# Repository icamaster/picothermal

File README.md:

# Introduction

Picothermal is a WebUSB thermal camera based on a Flir Lepton 3.5 sensor that uses a RP2040 and connects to your PC or phone via USB-C. 

It doesn't need any app as it uses WebUSB (which also means it doesn't support Firefox, unfortunately). 

*Top assembly*

[*WebUSB app*](#firmware)

# Hardware

The hardware and software is open-source, see the [picothermal-hardware](picothermal-hardware) folder for the Kicad project, manufacturing files and a PDF schematic. 

There are also STLs available for an enclosure in [enclosure](enclosure). There are two variants for the bottom piece depending on the PCB thickness (0.8mm or 1.6mm).

# Firmware

For firmware, please see [picothermal-fw](https://github.com/icamaster/picothermal-fw).

Initially I wanted to write the software in C, using TinyUSB for the USB protocol. Unfortunately, due to lack of free time, I decided to rewrite this using agents in Rust, using embassy. The end result works quite good, although I expect the code to be pretty unmaintanable since it is mostly agent written.

# License

MIT

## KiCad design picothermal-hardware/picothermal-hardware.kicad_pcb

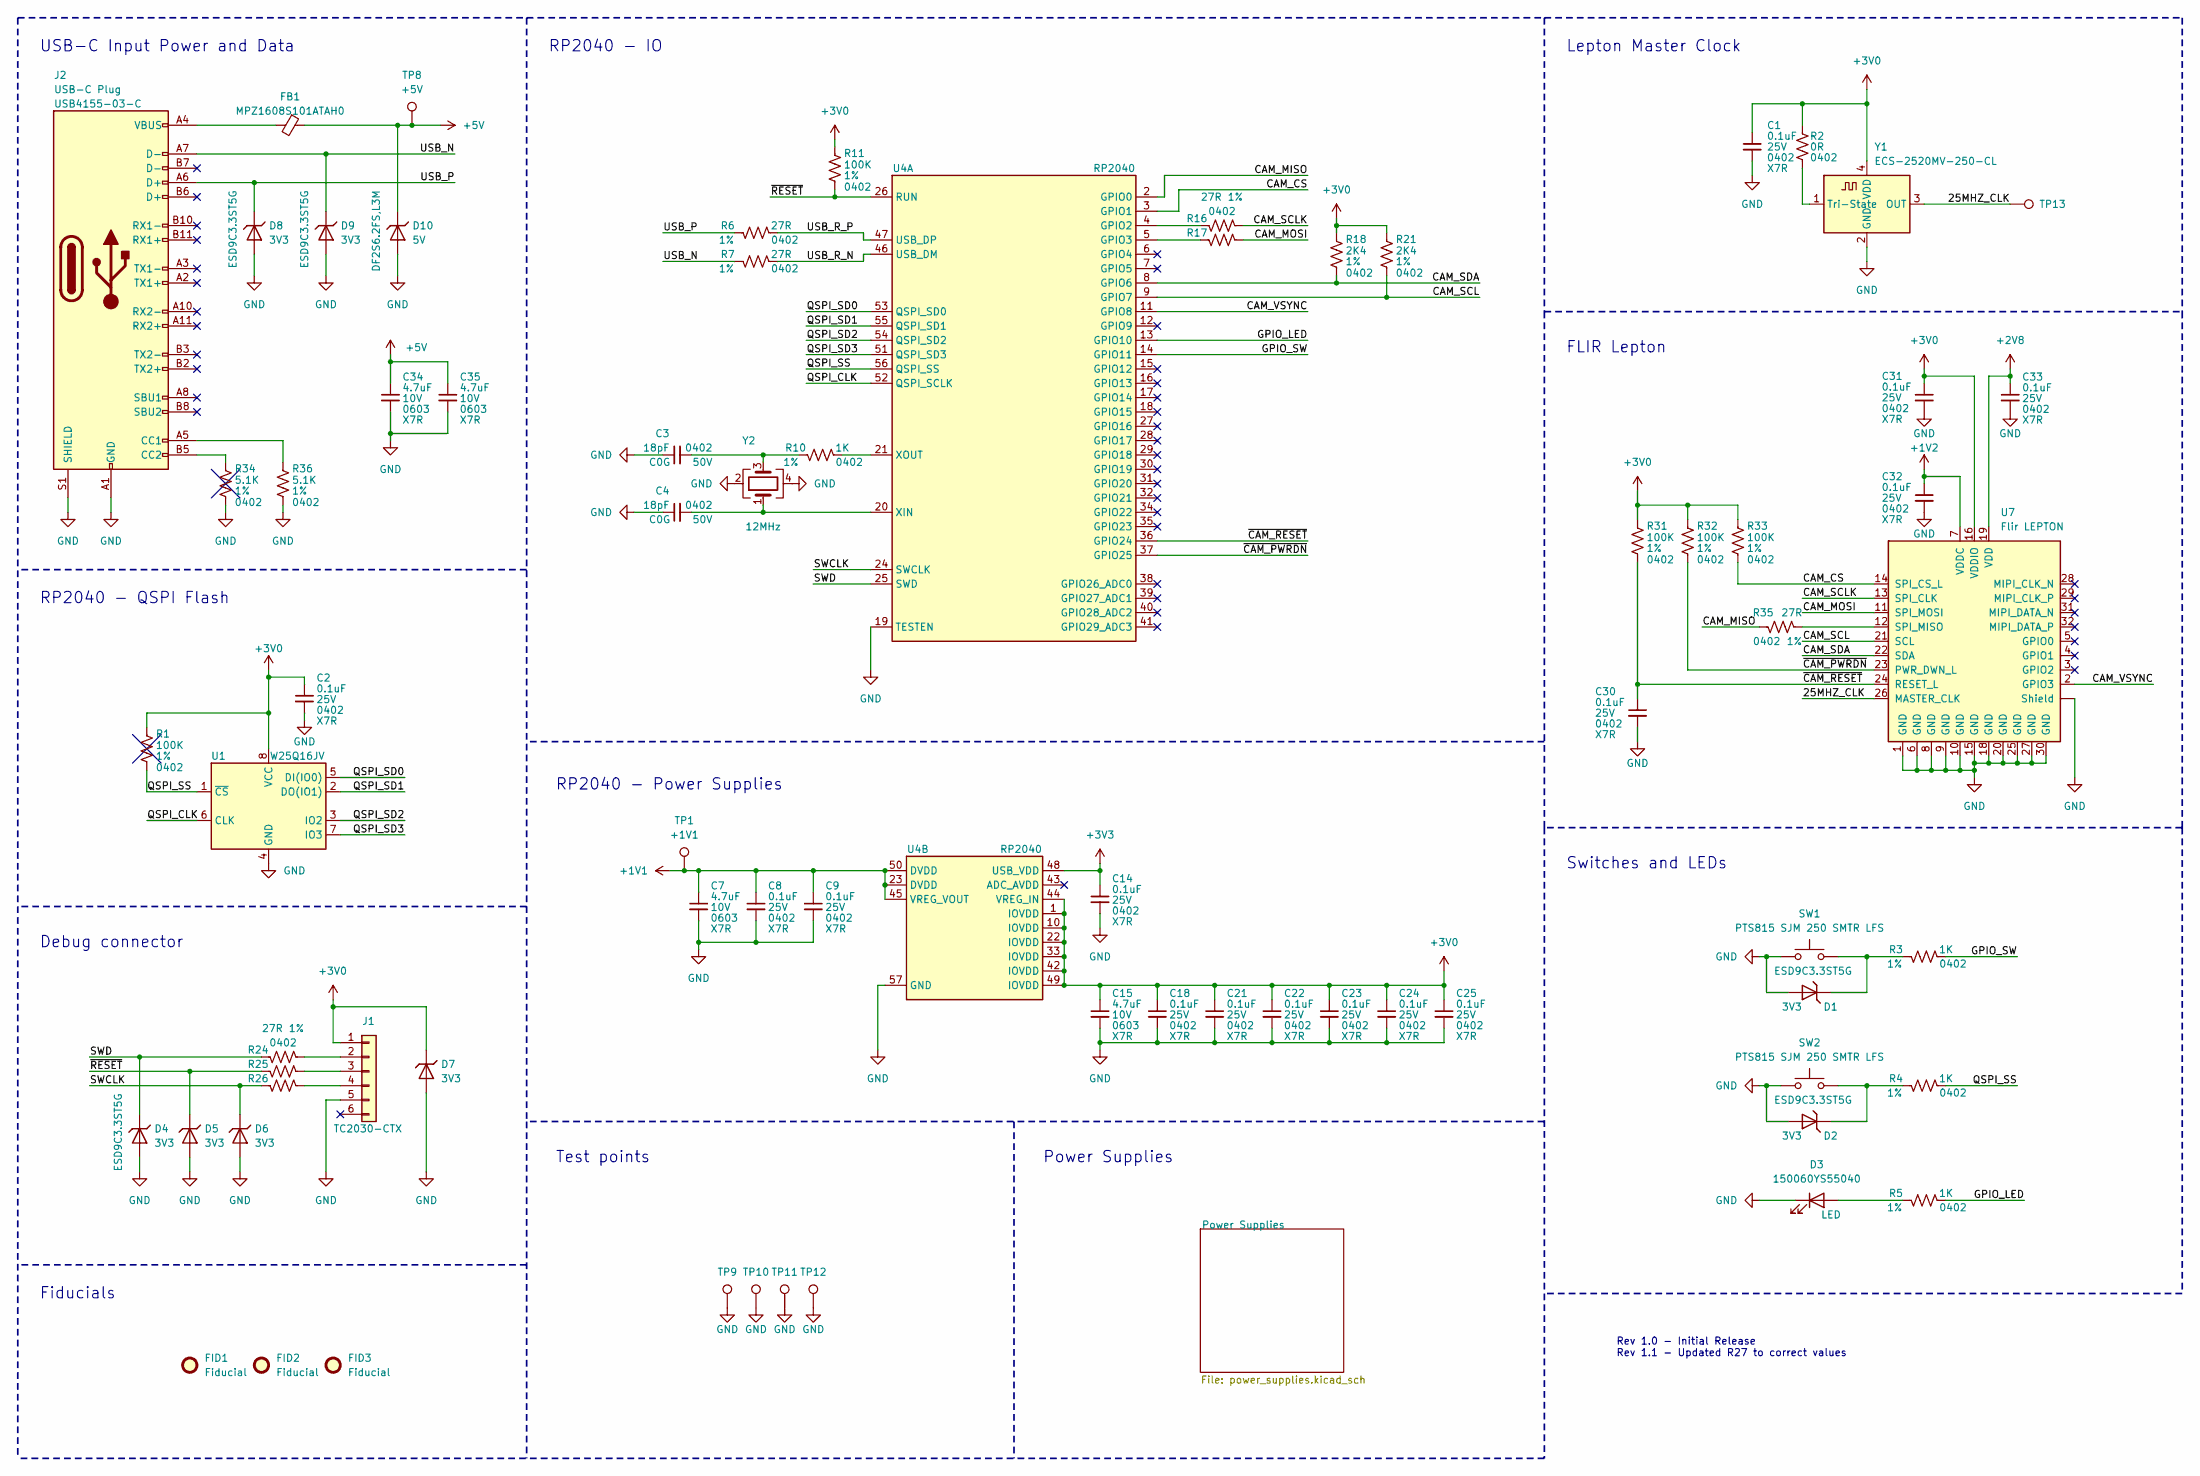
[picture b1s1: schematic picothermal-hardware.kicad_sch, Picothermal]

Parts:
C1, C2, C8, C9, C14, C18, C21, C22, C23, C24, C25, C30, C31, C32, C33: 0.1uF; C_0402_1005Metric; Voltage Rating 25V
C3, C4: 18pF; C_0402_1005Metric; Voltage Rating 50V
C7, C15, C34, C35: 4.7uF; C_0603_1608Metric; Voltage Rating 10V
D1, D2, D4, D5, D6, D7, D8, D9: ESD9C3.3ST5G; D_SOD-923; Part Number ESD9C3.3ST5G
D3: LED; LED_0603_1608Metric; Part Number 150060YS55040
D10: DF2S6.2FS,L3M; D_SOD-923; Part Number DF2S6.2FS,L3M
FB1: MPZ1608S101ATAH0; L_0603_1608Metric; Part Number MPZ1608S101ATAH0
FID1, FID2, FID3: Fiducial; Fiducial_1mm_Mask2mm
J1: TC2030-CTX; Tag-Connect_TC2030-IDC-NL_2x03_P1.27mm_Vertical
J2: USB-C Plug; USB_C_Plug_GCT_USB4155; Part Number USB4155-03-C
R1, R11, R31, R32, R33: 100K; R_0402_1005Metric; Tolerance 1%
R2: 0R; R_0402_1005Metric; Tolerance 1%
R3, R4, R5, R10: 1K; R_0402_1005Metric; Tolerance 1%
R6, R7, R16, R17, R24, R25, R26, R35: 27R; R_0402_1005Metric; Tolerance 1%
R18, R21: 2K4; R_0402_1005Metric; Tolerance 1%
R34, R36: 5.1K; R_0402_1005Metric; Tolerance 1%
SW1, SW2: SW_Push; SW_SPST_PTS815; Part Number PTS815 SJM 250 SMTR LFS
TP1: +1V1; TestPoint_Pad_D1.0mm
TP8: +5V; TestPoint_Pad_D1.0mm
TP9, TP10, TP12: GND; TestPoint_Pad_D1.0mm
TP11: GND; TestPoint_Plated_Slot_5.0x2.5
TP13: 25MHz; TestPoint_Pad_D1.0mm
U1: W25Q16JV; USON-8_2x3mm; Part Number W25Q16JVUXIQ
U4: RP2040; QFN-56-1EP_7x7mm_P0.4mm_EP3.2x3.2mm; Part Number RP2040
U7: Flir LEPTON; MOLEX_105028-1001; Part Number 105028-1001
Y1: ECS-2520MV-250-CL; Oscillator_SMD_ECS_2520MV-xxx-xx-4Pin_2.5x2.0mm
Y2: 12MHz; Crystal_SMD_2520-4Pin_2.5x2.0mm; Part Number ECS-120-12-36-AGN-TR3

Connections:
+1V1: C7.1, C8.1, C9.1, TP1.1, U4.23 (DVDD), U4.45 (VREG_VOUT), U4.50 (DVDD)
+1V2: C32.1, U7.7 (VDDC); also elsewhere on the board
+2V8: C33.1, U7.19 (VDD); also elsewhere on the board
+3V0: C1.1, C2.1, C15.1, C18.1, C21.1, C22.1, C23.1, C24.1, C25.1, C31.1, D7.1 (K), J1.1, R1.1, R2.1, R11.1, R18.1, R21.1, R31.1, R32.1, R33.1, U1.8 (VCC), U4.1 (IOVDD), U4.10 (IOVDD), U4.22 (IOVDD), U4.33 (IOVDD), U4.42 (IOVDD), U4.44 (VREG_IN), U4.49 (IOVDD), U7.16 (VDDIO), Y1.4 (VDD); also elsewhere on the board
+3V3: C14.1, U4.48 (USB_VDD); also elsewhere on the board
+5V: C34.1, C35.1, D10.1 (K), FB1.1, TP8.1; also elsewhere on the board
/25MHZ_CLK: TP13.1, U7.26 (MASTER_CLK), Y1.3 (OUT)
/CAM_CS: R33.2, U4.3 (GPIO1), U7.14 (SPI_CS_L)
/CAM_MISO: R35.2, U4.2 (GPIO0)
/CAM_MOSI: R17.1, U7.11 (SPI_MOSI)
/CAM_SCL: R21.2, U4.9 (GPIO7), U7.21 (SCL)
/CAM_SCLK: R16.1, U7.13 (SPI_CLK)
/CAM_SDA: R18.2, U4.8 (GPIO6), U7.22 (SDA)
/CAM_VSYNC: U4.11 (GPIO8), U7.2 (GPIO3)
/GPIO_LED: R5.1, U4.13 (GPIO10)
/GPIO_SW: R3.1, U4.14 (GPIO11)
/QSPI_CLK: U1.6 (CLK), U4.52 (QSPI_SCLK)
/QSPI_SD0: U1.5 (DI(IO0)), U4.53 (QSPI_SD0)
/QSPI_SD1: U1.2 (DO(IO1)), U4.55 (QSPI_SD1)
/QSPI_SD2: U1.3 (IO2), U4.54 (QSPI_SD2)
/QSPI_SD3: U1.7 (IO3), U4.51 (QSPI_SD3)
/QSPI_SS: R1.2, R4.1, U1.1 (~CS), U4.56 (QSPI_SS)
/SWCLK: D6.1 (K), R26.2, U4.24 (SWCLK)
/SWD: D4.1 (K), R24.2, U4.25 (SWD)
/USB_N: D9.1 (K), J2.A7 (D-), R7.2
/USB_P: D8.1 (K), J2.A6 (D+), R6.2
/USB_R_N: R7.1, U4.46 (USB_DM)
/USB_R_P: R6.1, U4.47 (USB_DP)
/~CAM_PWRDN: R32.2, U4.37 (GPIO25), U7.23 (PWR_DWN_L)
/~CAM_RESET: C30.1, R31.2, U4.36 (GPIO24), U7.24 (RESET_L)
/~RESET: D5.1 (K), R11.2, R25.2, U4.26 (RUN)
GND: C1.2, C2.2, C3.1, C4.1, C7.2, C8.2, C9.2, C14.2, C15.2, C18.2, C21.2, C22.2, C23.2, C24.2, C25.2, C30.2, C31.2, C32.2, C33.2, C34.2, C35.2, D1.2 (A), D2.2 (A), D3.1 (K), D4.2 (A), D5.2 (A), D6.2 (A), D7.2 (A), D8.2 (A), D9.2 (A), D10.2 (A), J1.5, J2.A1 (GND), J2.A12 (GND), J2.B1 (GND), J2.B12 (GND), J2.S1 (SHIELD), R34.2, R36.2, SW1.1, SW2.1, TP9.1, TP10.1, TP11.1, TP12.1, U1.4 (GND), U4.19 (TESTEN), U4.57 (GND), U7.1 (GND), U7.6 (GND), U7.8 (GND), U7.9 (GND), U7.10 (GND), U7.15 (GND), U7.17 (NC), U7.18 (GND), U7.20 (GND), U7.25 (GND), U7.27 (GND), U7.30 (GND), U7.Shield, Y1.2 (GND), Y2.2, Y2.4; also elsewhere on the board
unnamed: C3.2, R10.2, Y2.3
unnamed: D1.1 (K), R3.2, SW1.2
unnamed: D2.1 (K), R4.2, SW2.2
unnamed: D3.2 (A), R5.2
unnamed: FB1.2, J2.A4 (VBUS), J2.A9 (VBUS), J2.B4 (VBUS), J2.B9 (VBUS)
unnamed: J1.2, R24.1
unnamed: J1.3, R25.1
unnamed: J1.4, R26.1
unnamed: J2.A5 (CC1), R36.1
unnamed: J2.B5 (CC2), R34.1
unnamed: R16.2, U4.4 (GPIO2)
unnamed: R17.2, U4.5 (GPIO3)
unnamed: C4.2, U4.20 (XIN), Y2.1
unnamed: R10.1, U4.21 (XOUT)
unnamed: R35.1, U7.12 (SPI_MISO)
unnamed: R2.2, Y1.1 (Tri-State)

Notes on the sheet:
Rev 1.0 - Initial Release Rev 1.1 - Updated R27 to correct values
FLIR Lepton
RP2040 - QSPI Flash
Test points
USB-C Input Power and Data
Fiducials
RP2040 - Power Supplies
Debug connector
Lepton Master Clock
RP2040 - IO
Switches and LEDs
Power Supplies

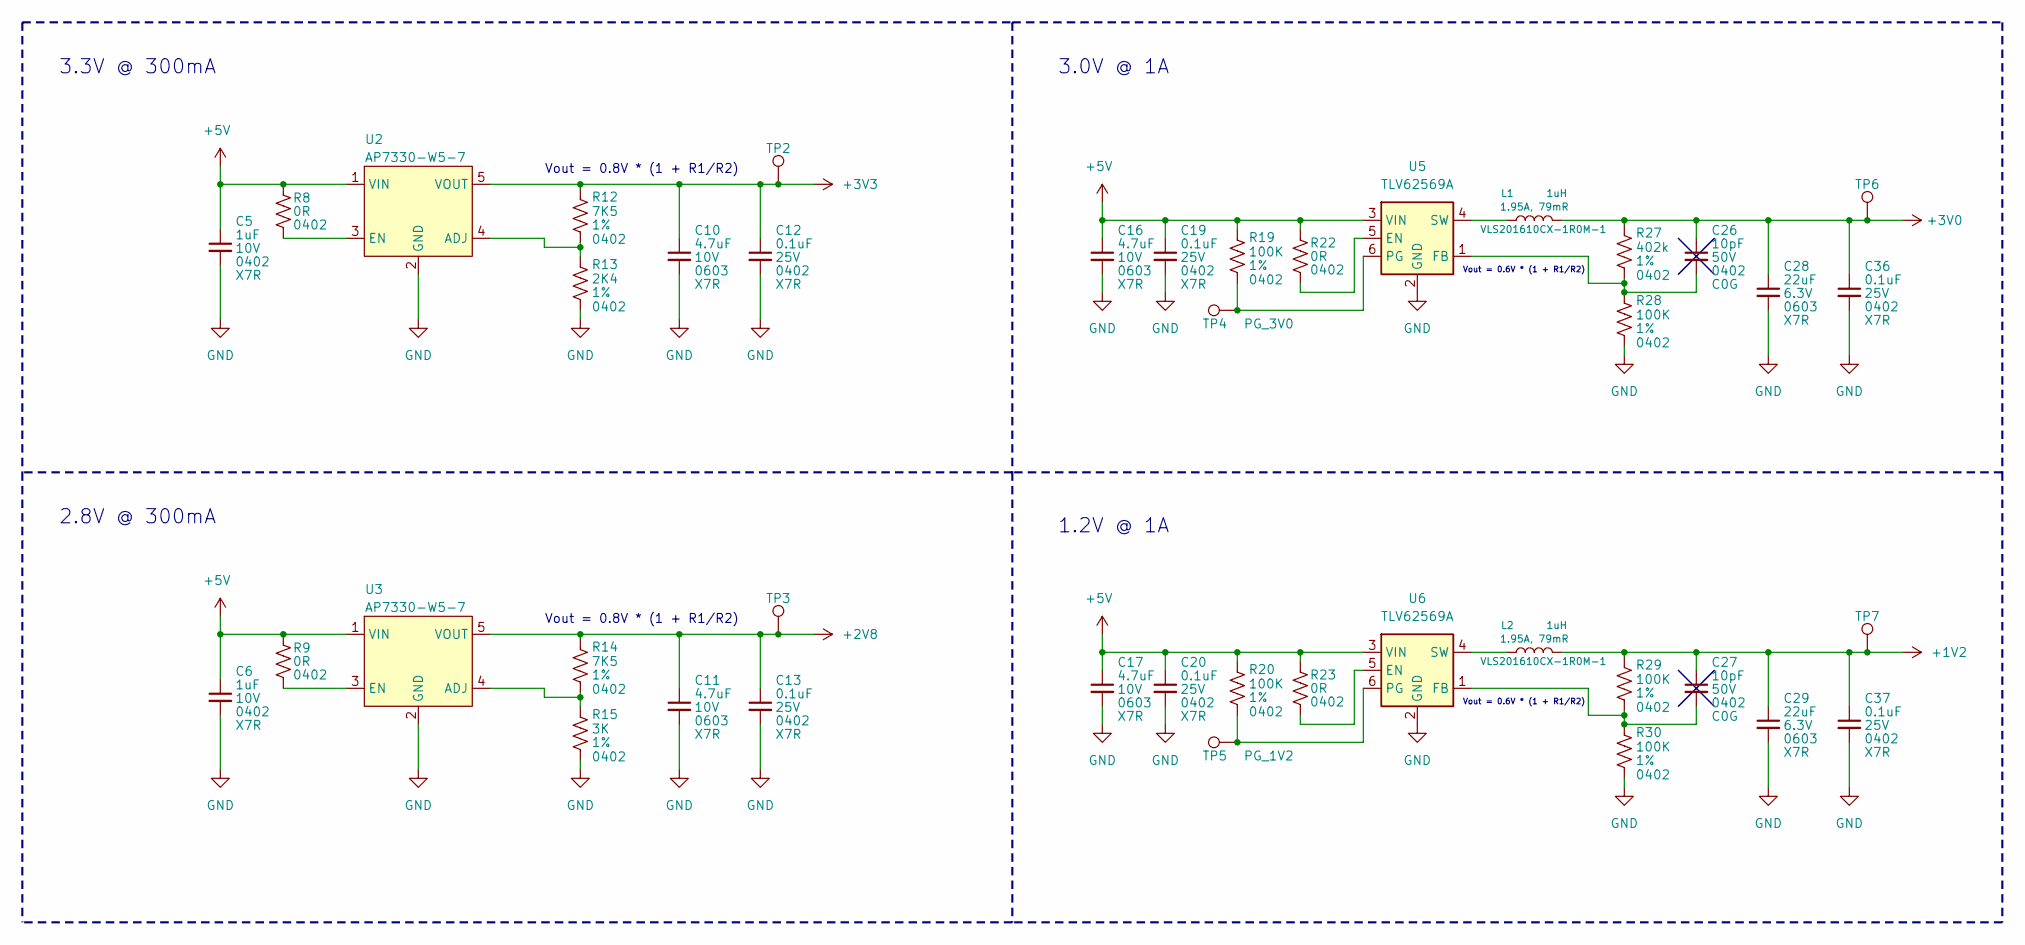
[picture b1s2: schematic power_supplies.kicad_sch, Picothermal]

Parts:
C5, C6: 1uF; C_0402_1005Metric; Voltage Rating 10V
C10, C11, C16, C17: 4.7uF; C_0603_1608Metric; Voltage Rating 10V
C12, C13, C19, C20, C36, C37: 0.1uF; C_0402_1005Metric; Voltage Rating 25V
C26, C27: 10pF; C_0402_1005Metric; Voltage Rating 50V
C28, C29: 22uF; C_0603_1608Metric; Voltage Rating 6.3V
L1, L2: 1uH; L_TDK_VLS201610CX-1; Part Number VLS201610CX-1R0M-1
R8, R9, R22, R23: 0R; R_0402_1005Metric; Tolerance 1%
R12, R14: 7K5; R_0402_1005Metric; Tolerance 1%
R13: 2K4; R_0402_1005Metric; Tolerance 1%
R15: 3K; R_0402_1005Metric; Tolerance 1%
R19, R20, R28, R29, R30: 100K; R_0402_1005Metric; Tolerance 1%
R27: 402k; R_0402_1005Metric; Tolerance 1%
TP2: 3V3; TestPoint_Pad_D1.0mm
TP3: 2V8; TestPoint_Pad_D1.0mm
TP4: PG_3V0; TestPoint_Pad_D1.0mm
TP5: PG_1V2; TestPoint_Pad_D1.0mm
TP6: 3V0; TestPoint_Pad_D1.0mm
TP7: 1V2; TestPoint_Pad_D1.0mm
U2, U3: AP7330-W5-7; SOT-25-5; Part Number AP7330-W5-7
U5, U6: TLV62569A; SOT-563; Part Number TLV62569APDRLR

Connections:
+1V2: C27.1, C29.1, C37.1, L2.2, R29.1, TP7.1; also elsewhere on the board
+2V8: C11.1, C13.1, R14.1, TP3.1, U3.5 (VOUT); also elsewhere on the board
+3V0: C26.1, C28.1, C36.1, L1.2, R27.1, TP6.1; also elsewhere on the board
+3V3: C10.1, C12.1, R12.1, TP2.1, U2.5 (VOUT); also elsewhere on the board
+5V: C5.1, C6.1, C16.1, C17.1, C19.1, C20.1, R8.1, R9.1, R19.1, R20.1, R22.1, R23.1, U2.1 (VIN), U3.1 (VIN), U5.3 (VIN), U6.3 (VIN); also elsewhere on the board
GND: C5.2, C6.2, C10.2, C11.2, C12.2, C13.2, C16.2, C17.2, C19.2, C20.2, C28.2, C29.2, C36.2, C37.2, R13.2, R15.2, R28.2, R30.2, U2.2 (GND), U3.2 (GND), U5.2 (GND), U6.2 (GND); also elsewhere on the board
unnamed: R12.2, R13.1, U2.4 (ADJ)
unnamed: R8.2, U2.3 (EN)
unnamed: R14.2, R15.1, U3.4 (ADJ)
unnamed: R9.2, U3.3 (EN)
unnamed: R22.2, U5.5 (EN)
unnamed: C26.2, R27.2, R28.1, U5.1 (FB)
unnamed: R19.2, TP4.1, U5.6 (PG)
unnamed: L1.1, U5.4 (SW)
unnamed: R23.2, U6.5 (EN)
unnamed: C27.2, R29.2, R30.1, U6.1 (FB)
unnamed: R20.2, TP5.1, U6.6 (PG)
unnamed: L2.1, U6.4 (SW)

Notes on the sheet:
2.8V @ 300mA
Vout = 0.8V * (1 + R1/R2)
3.0V @ 1A
Vout = 0.6V * (1 + R1/R2)
1.2V @ 1A
3.3V @ 300mA

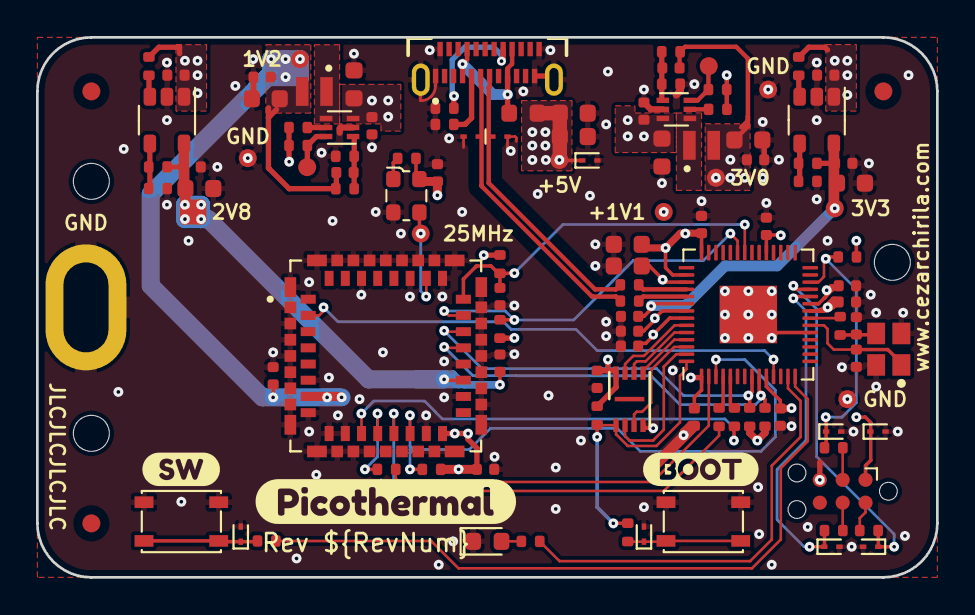
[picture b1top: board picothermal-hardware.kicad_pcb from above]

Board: 4 copper layers, 50.0 x 30.0 mm, 118 parts (0 on the bottom side), 60 nets.

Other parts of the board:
kibuzzard-63AA0E75: G***; kibuzzard-63AA0E75
kibuzzard-63AA0EB3: G***; kibuzzard-63AA0EB3
kibuzzard-63AA0F05: G***; kibuzzard-63AA0F05

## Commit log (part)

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2022-12-26 PCB Layout is now complete
2022-12-27 Final review passed and added fabrication outputs
2022-12-28 Updated minimum clearance
2023-02-02 Regenerate output using latest version and add step and interactive BOM
2023-03-04 Regenerate hardware files
2023-03-04 Start work on picothermal firmware
2023-03-19 Updated hardware project to work with Kicad 7.0
2023-03-19 Add USB example
2023-08-13 Update repo settings
2023-08-13 Small changes to descriptors
